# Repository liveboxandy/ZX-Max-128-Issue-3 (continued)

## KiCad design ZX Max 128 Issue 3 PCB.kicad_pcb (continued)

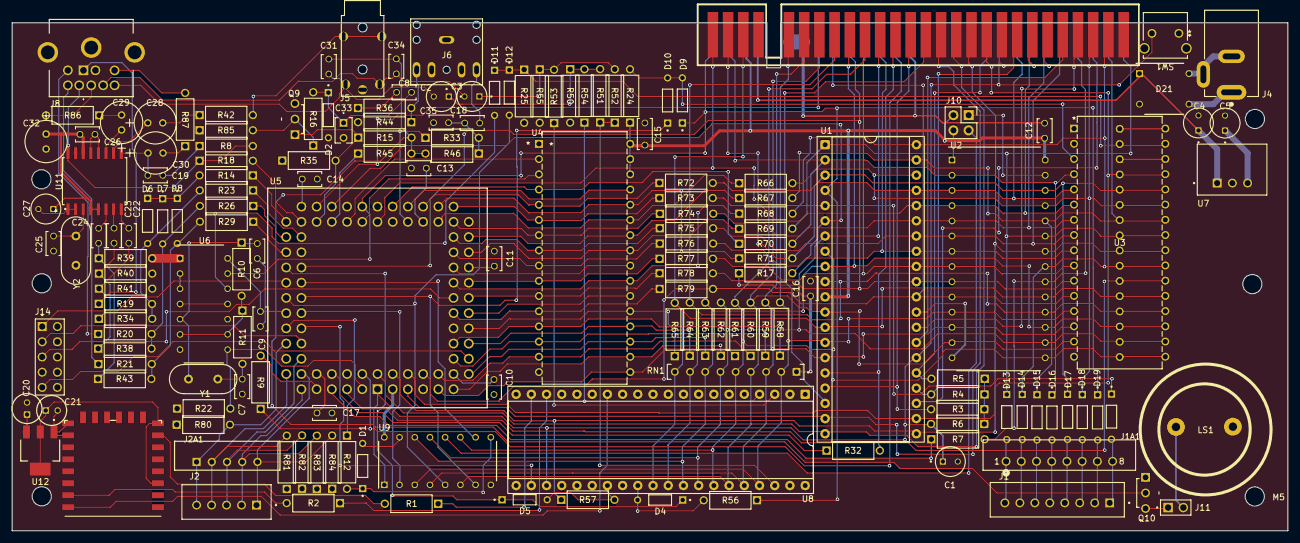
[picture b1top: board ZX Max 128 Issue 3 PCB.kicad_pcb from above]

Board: 2 copper layers, 213.0 x 84.8 mm, 170 parts (0 on the bottom side), 172 nets.

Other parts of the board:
C2, C3: 10uF 25V; CAPPRD200W50D500H1100
D4, D5: 1N4148; DIOAD753W49L380D172B
J5: AV Jack; PJ-322A
R1, R2, R56, R57: 470R; STA_CF14_STP
R50, R53, R54, R55: 1K00; STA_CF14_STP
R51, R52: 2K20; STA_CF14_STP
U8: AY-3-8910; Z80_Socket
U15: ESP8266-12E; WIFI_Module_ESP8266_12E

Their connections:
+3V3D: U15.3 (EN), U15.8 (VCC); also elsewhere on the board
/Turbo Sound/L-in: C3.1 (+), R52.2, R53.2, R55.1
/Turbo Sound/R-in: C2.1 (+), R50.2, R51.2, R54.1
A14: R56.1; also elsewhere on the board
A-AY: R50.1, U8.4 (CHANNEL_A)
Audio-L: C3.2 (-), J5.2; also elsewhere on the board
Audio-R: C2.2 (-), J5.4; also elsewhere on the board
B-AY: R53.1, U8.3 (CHANNEL_B)
BC1: D4.A, R56.2, U8.29 (BC1)
BDIR: D5.A, R57.2, U8.27 (BDIR)
C-AY: R51.1, R52.1, U8.38 (CHANNEL_C)
CLKAY: U8.22 (CLK); also elsewhere on the board
Comp: J5.3; also elsewhere on the board
D0: U8.37 (DA0); also elsewhere on the board
D1: U8.36 (DA1); also elsewhere on the board
D2: U8.35 (DA2); also elsewhere on the board
D3: U8.34 (DA3); also elsewhere on the board
D4: U8.33 (DA4); also elsewhere on the board
D5: U8.32 (DA5); also elsewhere on the board
D6: U8.31 (DA6); also elsewhere on the board
D7: U8.30 (DA7); also elsewhere on the board
GND: J5.1, R54.2, R55.2, U8.1 (VSS), U8.24 (~A9), U15.15 (GND), U15.16 (TXD2/IO15); also elsewhere on the board
IN4: U8.14 (IOA7), U15.22 (TXD0/TXD)
MIDI: R1.2, U15.7 (MOSI/IO13)
unnamed: R2.2, U15.21 (RXD0/RXD)
OUT3: R1.1, U8.19 (IOA2)
OUT4: R2.1, U8.18 (IOA3)
PSG: D4.K, D5.K; also elsewhere on the board
RD: R57.1; also elsewhere on the board
RST: U8.23 (~RESET); also elsewhere on the board
VCC: U8.25 (A8), U8.28 (BC2), U8.40 (VCC); also elsewhere on the board
